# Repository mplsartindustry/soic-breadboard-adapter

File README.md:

# soic-breadboard-adapter

Adapter PCB for SOIC-16 surface mount ICs to be used in a breadboard

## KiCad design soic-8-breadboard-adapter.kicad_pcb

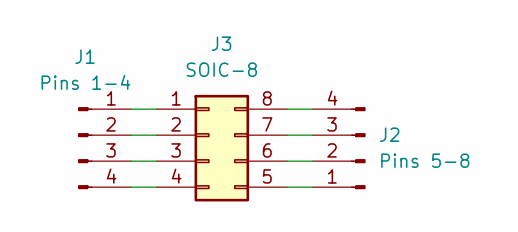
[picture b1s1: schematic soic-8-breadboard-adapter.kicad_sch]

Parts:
J1: Pins 1-4; PinHeader_1x04_P2.54mm_Vertical
J2: Pins 5-8; PinHeader_1x04_P2.54mm_Vertical
J3: SOIC-8; SOIC-8_3.9x4.9mm_P1.27mm

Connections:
unnamed: J1.1, J3.1
unnamed: J1.2, J3.2
unnamed: J1.3, J3.3
unnamed: J1.4, J3.4
unnamed: J2.1, J3.5
unnamed: J2.2, J3.6
unnamed: J2.3, J3.7
unnamed: J2.4, J3.8

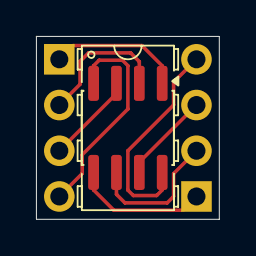
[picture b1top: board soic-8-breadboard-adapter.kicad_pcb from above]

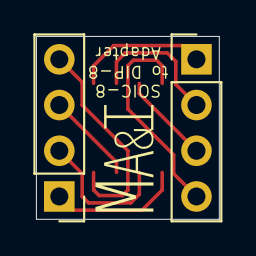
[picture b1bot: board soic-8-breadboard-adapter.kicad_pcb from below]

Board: 2 copper layers, 10.2 x 10.2 mm, 3 parts (2 on the bottom side), 8 nets.

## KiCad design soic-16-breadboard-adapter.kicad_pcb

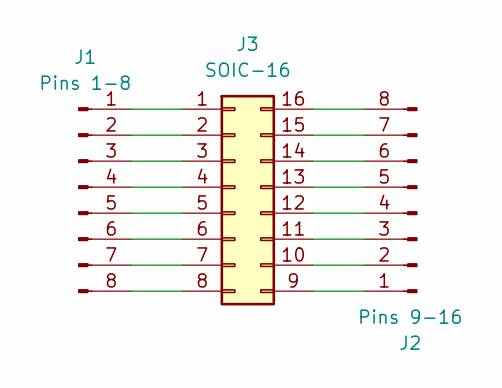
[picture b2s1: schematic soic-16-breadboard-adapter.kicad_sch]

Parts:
J1: Pins 1-8; PinHeader_1x08_P2.54mm_Vertical
J2: Pins 9-16; PinHeader_1x08_P2.54mm_Vertical
J3: SOIC-16; SOIC-16_3.9x9.9mm_P1.27mm

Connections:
unnamed: J1.1, J3.1
unnamed: J1.2, J3.2
unnamed: J1.3, J3.3
unnamed: J1.4, J3.4
unnamed: J1.5, J3.5
unnamed: J1.6, J3.6
unnamed: J1.7, J3.7
unnamed: J1.8, J3.8
unnamed: J2.1, J3.9
unnamed: J2.2, J3.10
unnamed: J2.3, J3.11
unnamed: J2.4, J3.12
unnamed: J2.5, J3.13
unnamed: J2.6, J3.14
unnamed: J2.7, J3.15
unnamed: J2.8, J3.16

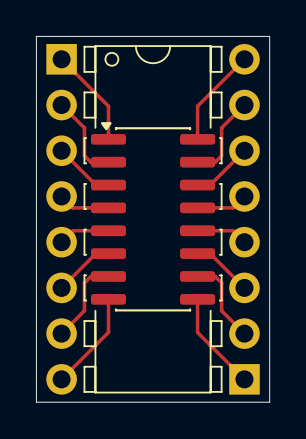
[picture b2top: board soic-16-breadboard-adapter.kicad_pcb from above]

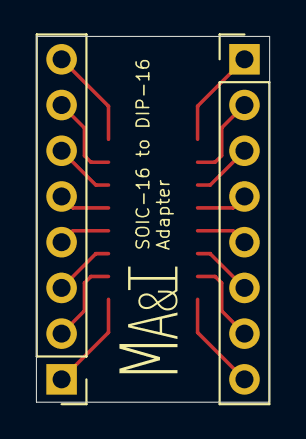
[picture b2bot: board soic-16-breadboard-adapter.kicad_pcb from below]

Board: 2 copper layers, 13.0 x 20.3 mm, 3 parts (2 on the bottom side), 16 nets.

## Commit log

2026-01-02 Export gerbers
2026-04-01 Rename project to soic-16-breadboard-adapter
2026-04-01 Update project
2026-04-01 Add SOIC-8 adapter
